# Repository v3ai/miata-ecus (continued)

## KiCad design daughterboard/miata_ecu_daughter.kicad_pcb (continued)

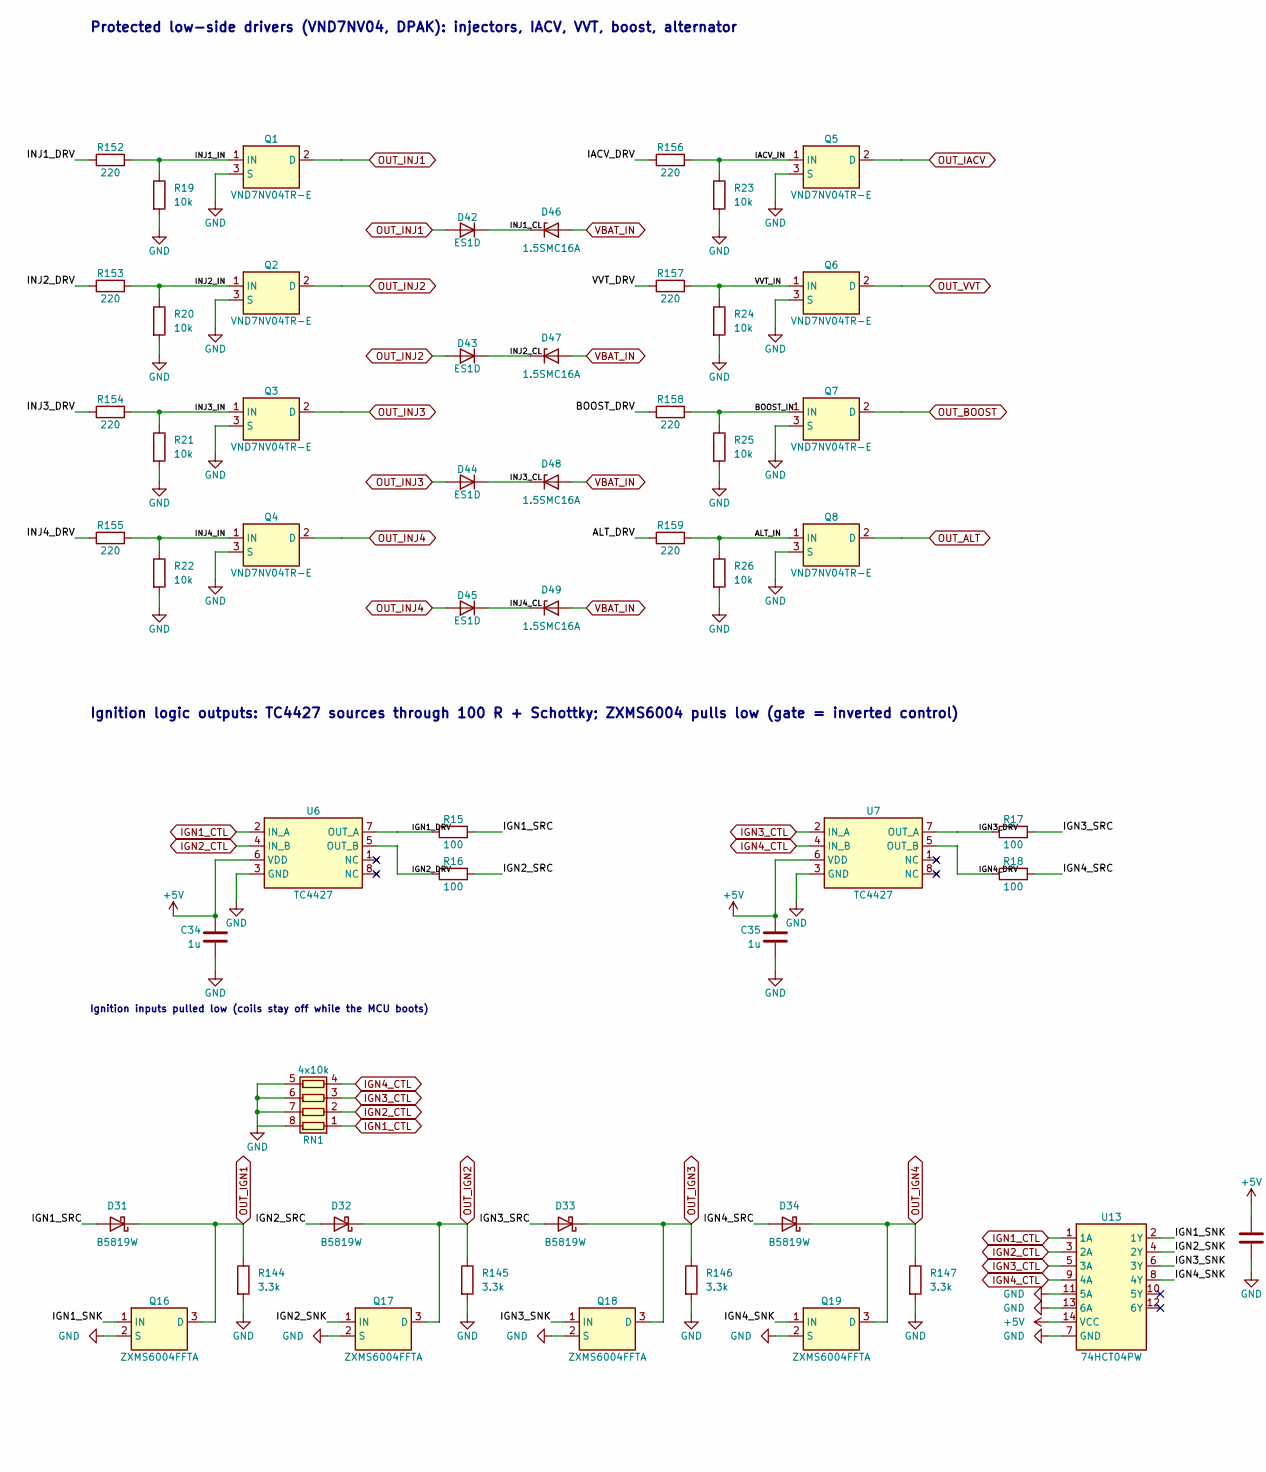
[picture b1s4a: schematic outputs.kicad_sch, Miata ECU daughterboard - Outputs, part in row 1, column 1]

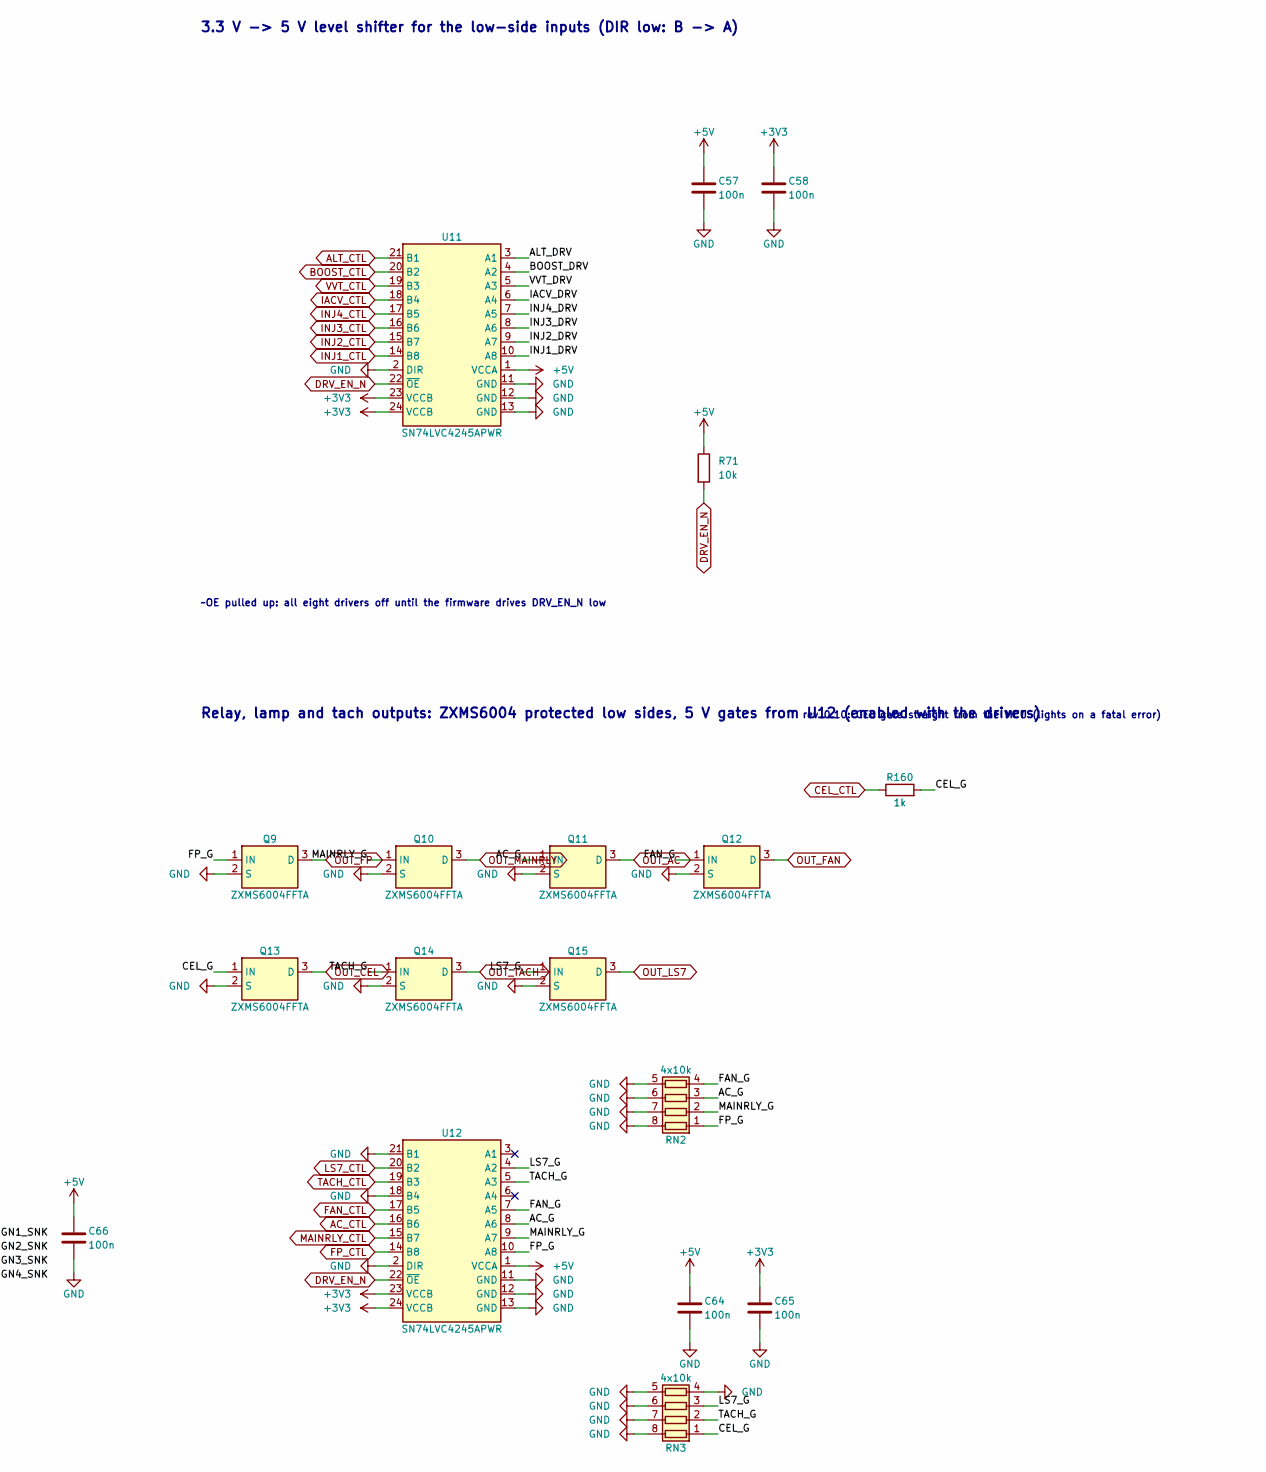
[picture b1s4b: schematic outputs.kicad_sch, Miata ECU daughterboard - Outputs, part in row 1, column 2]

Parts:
C34, C35: 1u; C_0402_1005Metric; LCSC C52923
C57, C58, C64, C65, C66: 100n; C_0402_1005Metric; LCSC C1525
D31, D32, D33, D34: B5819W; D_SOD-123; LCSC C8598
D42, D43, D44, D45: ES1D; D_SMA; LCSC C116492
D46, D47, D48, D49: 1.5SMC16A; D_SMC; LCSC C1973780
Q1, Q2, Q3, Q4, Q5, Q6, Q7, Q8: VND7NV04TR-E; TO-252-2; LCSC C155605
Q9, Q10, Q11, Q12, Q13, Q14, Q15, Q16, Q17, Q18, Q19: ZXMS6004FFTA; SOT-23; LCSC C95063
R15, R16, R17, R18: 100; R_1206_3216Metric; LCSC C17901
R19, R20, R21, R22, R23, R24, R25, R26: 10k; R_0603_1608Metric; LCSC C25804
R71: 10k; R_0402_1005Metric; LCSC C25744
R144, R145, R146, R147: 3.3k; R_1206_3216Metric; LCSC C26032
R152, R153, R154, R155, R156, R157, R158, R159: 220; R_0402_1005Metric; LCSC C25091
R160: 1k; R_0402_1005Metric; LCSC C11702
RN1, RN2, RN3: 4x10k; R_Array_Convex_4x0603; LCSC C29718
U6, U7: TC4427; SOIC-8_3.9x4.9mm_P1.27mm; LCSC C20551
U11, U12: SN74LVC4245APWR; TSSOP-24_4.4x7.8mm_P0.65mm; LCSC C7859
U13: 74HCT04PW; TSSOP-14_4.4x5mm_P0.65mm; LCSC C131317

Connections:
+3V3: C58.1, C65.1, U11.23 (VCCB), U11.24 (VCCB), U12.23 (VCCB), U12.24 (VCCB); also elsewhere on the board
+5V: C34.1, C35.1, C57.1, C64.1, C66.1, R71.1, U6.6 (VDD), U7.6 (VDD), U11.1 (VCCA), U12.1 (VCCA), U13.14 (VCC); also elsewhere on the board
/Outputs/AC_G: Q11.1 (IN), RN2.3 (R3.1), U12.8 (A6)
/Outputs/ALT_DRV: R159.1, U11.3 (A1)
/Outputs/ALT_IN: Q8.1 (IN), R26.1, R159.2
/Outputs/BOOST_DRV: R158.1, U11.4 (A2)
/Outputs/BOOST_IN: Q7.1 (IN), R25.1, R158.2
/Outputs/CEL_G: Q13.1 (IN), R160.2, RN3.1 (R1.1)
/Outputs/FAN_G: Q12.1 (IN), RN2.4 (R4.1), U12.7 (A5)
/Outputs/FP_G: Q9.1 (IN), RN2.1 (R1.1), U12.10 (A8)
/Outputs/IACV_DRV: R156.1, U11.6 (A4)
/Outputs/IACV_IN: Q5.1 (IN), R23.1, R156.2
/Outputs/IGN1_DRV: R15.1, U6.7 (OUT_A)
/Outputs/IGN1_SNK: Q16.1 (IN), U13.2 (1Y)
/Outputs/IGN1_SRC: D31.2 (A), R15.2
/Outputs/IGN2_DRV: R16.1, U6.5 (OUT_B)
/Outputs/IGN2_SNK: Q17.1 (IN), U13.4 (2Y)
/Outputs/IGN2_SRC: D32.2 (A), R16.2
/Outputs/IGN3_DRV: R17.1, U7.7 (OUT_A)
/Outputs/IGN3_SNK: Q18.1 (IN), U13.6 (3Y)
/Outputs/IGN3_SRC: D33.2 (A), R17.2
/Outputs/IGN4_DRV: R18.1, U7.5 (OUT_B)
/Outputs/IGN4_SNK: Q19.1 (IN), U13.8 (4Y)
/Outputs/IGN4_SRC: D34.2 (A), R18.2
/Outputs/INJ1_CL: D42.1 (K), D46.1 (K)
/Outputs/INJ1_DRV: R152.1, U11.10 (A8)
/Outputs/INJ1_IN: Q1.1 (IN), R19.1, R152.2
/Outputs/INJ2_CL: D43.1 (K), D47.1 (K)
/Outputs/INJ2_DRV: R153.1, U11.9 (A7)
/Outputs/INJ2_IN: Q2.1 (IN), R20.1, R153.2
/Outputs/INJ3_CL: D44.1 (K), D48.1 (K)
/Outputs/INJ3_DRV: R154.1, U11.8 (A6)
/Outputs/INJ3_IN: Q3.1 (IN), R21.1, R154.2
/Outputs/INJ4_CL: D45.1 (K), D49.1 (K)
/Outputs/INJ4_DRV: R155.1, U11.7 (A5)
/Outputs/INJ4_IN: Q4.1 (IN), R22.1, R155.2
/Outputs/LS7_G: Q15.1 (IN), RN3.3 (R3.1), U12.4 (A2)
/Outputs/MAINRLY_G: Q10.1 (IN), RN2.2 (R2.1), U12.9 (A7)
/Outputs/TACH_G: Q14.1 (IN), RN3.2 (R2.1), U12.5 (A3)
/Outputs/VVT_DRV: R157.1, U11.5 (A3)
/Outputs/VVT_IN: Q6.1 (IN), R24.1, R157.2
AC_CTL: U12.16 (B6); also elsewhere on the board
ALT_CTL: U11.21 (B1); also elsewhere on the board
BOOST_CTL: U11.20 (B2); also elsewhere on the board
CEL_CTL: R160.1; also elsewhere on the board
DRV_EN_N: R71.2, U11.22 (~OE), U12.22 (~OE); also elsewhere on the board
FAN_CTL: U12.17 (B5); also elsewhere on the board
FP_CTL: U12.14 (B8); also elsewhere on the board
GND: C34.2, C35.2, C57.2, C58.2, C64.2, C65.2, C66.2, Q1.3 (S), Q2.3 (S), Q3.3 (S), Q4.3 (S), Q5.3 (S), Q6.3 (S), Q7.3 (S), Q8.3 (S), Q9.2 (S), Q10.2 (S), Q11.2 (S), Q12.2 (S), Q13.2 (S), Q14.2 (S), Q15.2 (S), Q16.2 (S), Q17.2 (S), Q18.2 (S), Q19.2 (S), R19.2, R20.2, R21.2, R22.2, R23.2, R24.2, R25.2, R26.2, R144.2, R145.2, R146.2, R147.2, RN1.5 (R4.2), RN1.6 (R3.2), RN1.7 (R2.2), RN1.8 (R1.2), RN2.5 (R4.2), RN2.6 (R3.2), RN2.7 (R2.2), RN2.8 (R1.2), RN3.4 (R4.1), RN3.5 (R4.2), RN3.6 (R3.2), RN3.7 (R2.2), RN3.8 (R1.2), U6.3 (GND), U7.3 (GND), U11.2 (DIR), U11.11 (GND), U11.12 (GND), U11.13 (GND), U12.2 (DIR), U12.11 (GND), U12.12 (GND), U12.13 (GND), U12.18 (B4), U12.21 (B1), U13.7 (GND), U13.11 (5A), U13.13 (6A); also elsewhere on the board
IACV_CTL: U11.18 (B4); also elsewhere on the board
IGN1_CTL: RN1.1 (R1.1), U6.2 (IN_A), U13.1 (1A); also elsewhere on the board
IGN2_CTL: RN1.2 (R2.1), U6.4 (IN_B), U13.3 (2A); also elsewhere on the board
IGN3_CTL: RN1.3 (R3.1), U7.2 (IN_A), U13.5 (3A); also elsewhere on the board
IGN4_CTL: RN1.4 (R4.1), U7.4 (IN_B), U13.9 (4A); also elsewhere on the board
INJ1_CTL: U11.14 (B8); also elsewhere on the board
INJ2_CTL: U11.15 (B7); also elsewhere on the board
INJ3_CTL: U11.16 (B6); also elsewhere on the board
INJ4_CTL: U11.17 (B5); also elsewhere on the board
LS7_CTL: U12.20 (B2); also elsewhere on the board
MAINRLY_CTL: U12.15 (B7); also elsewhere on the board
OUT_AC: Q11.3 (D); also elsewhere on the board
OUT_ALT: Q8.2 (D); also elsewhere on the board
OUT_BOOST: Q7.2 (D); also elsewhere on the board
OUT_CEL: Q13.3 (D); also elsewhere on the board
OUT_FAN: Q12.3 (D); also elsewhere on the board
OUT_FP: Q9.3 (D); also elsewhere on the board
OUT_IACV: Q5.2 (D); also elsewhere on the board
OUT_IGN1: D31.1 (K), Q16.3 (D), R144.1; also elsewhere on the board
OUT_IGN2: D32.1 (K), Q17.3 (D), R145.1; also elsewhere on the board
OUT_IGN3: D33.1 (K), Q18.3 (D), R146.1; also elsewhere on the board
OUT_IGN4: D34.1 (K), Q19.3 (D), R147.1; also elsewhere on the board
OUT_INJ1: D42.2 (A), Q1.2 (D); also elsewhere on the board
OUT_INJ2: D43.2 (A), Q2.2 (D); also elsewhere on the board
OUT_INJ3: D44.2 (A), Q3.2 (D); also elsewhere on the board
OUT_INJ4: D45.2 (A), Q4.2 (D); also elsewhere on the board
OUT_LS7: Q15.3 (D); also elsewhere on the board
OUT_MAINRLY: Q10.3 (D); also elsewhere on the board
OUT_TACH: Q14.3 (D); also elsewhere on the board
OUT_VVT: Q6.2 (D); also elsewhere on the board
TACH_CTL: U12.19 (B3); also elsewhere on the board
VBAT_IN: D46.2 (A), D47.2 (A), D48.2 (A), D49.2 (A); also elsewhere on the board
VVT_CTL: U11.19 (B3); also elsewhere on the board

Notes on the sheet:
Protected low-side drivers (VND7NV04, DPAK): injectors, IACV, VVT, boost, alternator
Ignition logic outputs: TC4427 sources through 100 R + Schottky; ZXMS6004 pulls low (gate = inverted control)
Ignition inputs pulled low (coils stay off while the MCU boots)
Relay, lamp and tach outputs: ZXMS6004 protected low sides, 5 V gates from U12 (enabled with the drivers)
rev 0.10: CEL gate straight from the MCU (lights on a fatal error)
3.3 V -> 5 V level shifter for the low-side inputs (DIR low: B -> A)
~OE pulled up: all eight drivers off until the firmware drives DRV_EN_N low

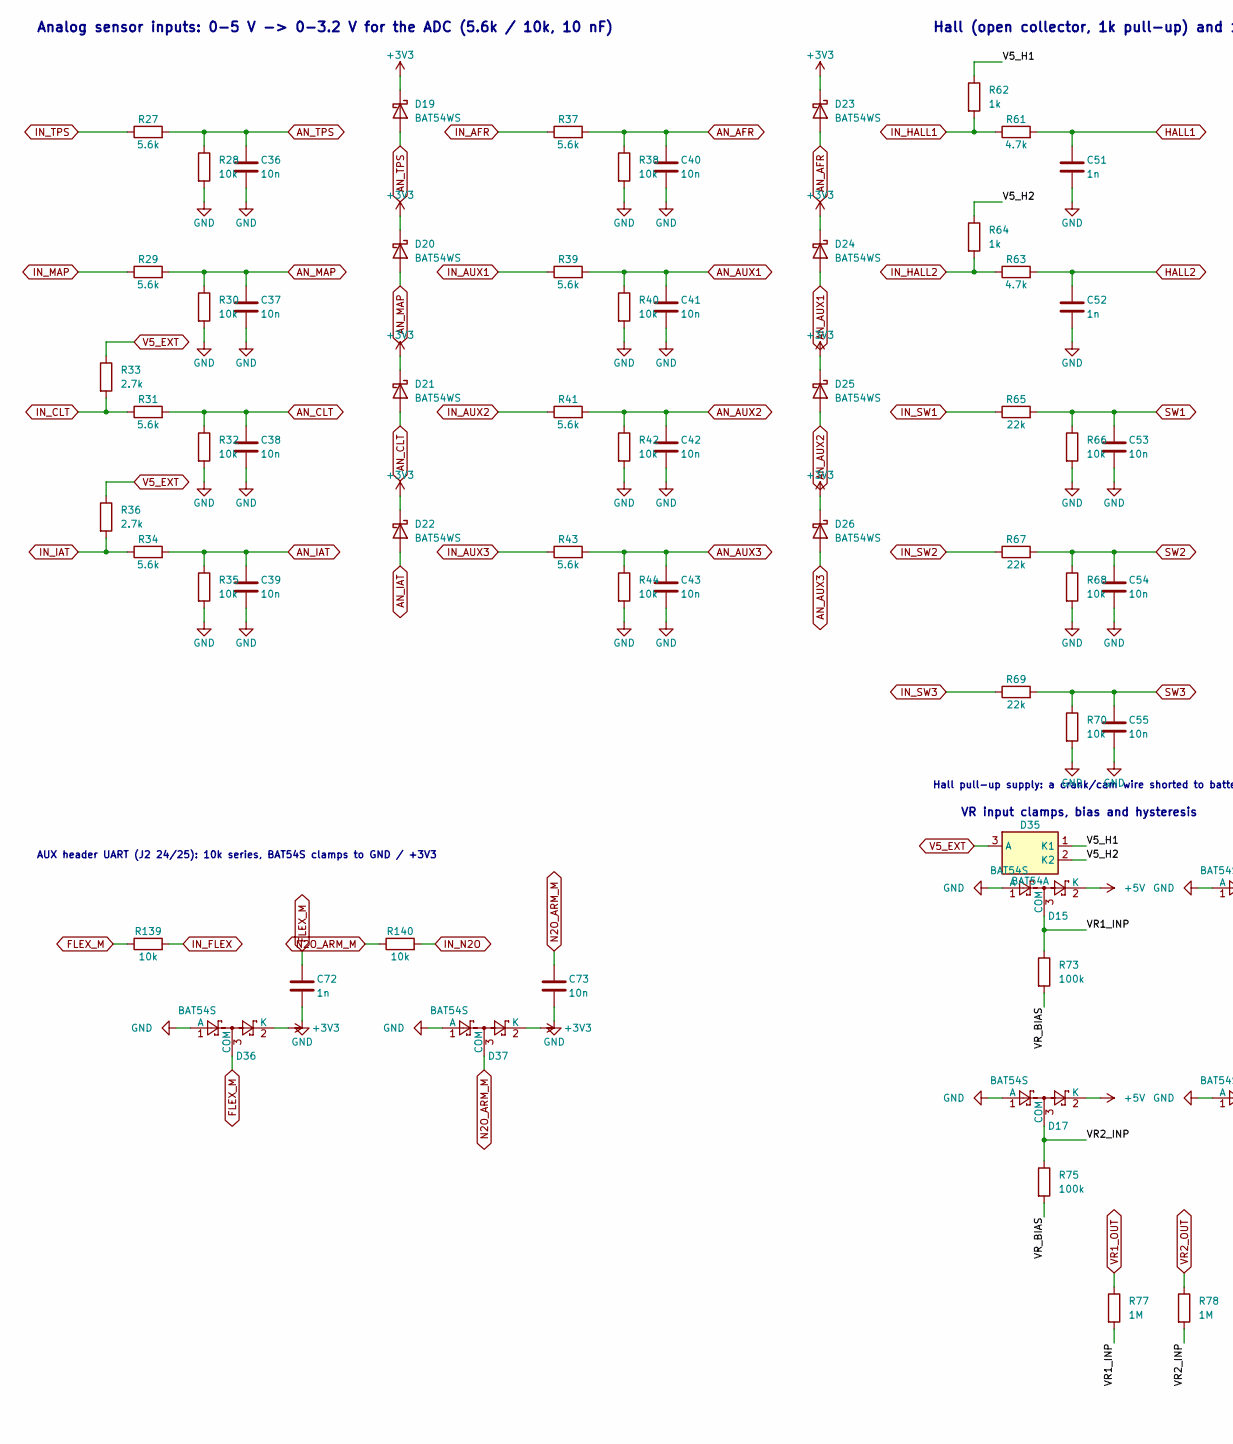
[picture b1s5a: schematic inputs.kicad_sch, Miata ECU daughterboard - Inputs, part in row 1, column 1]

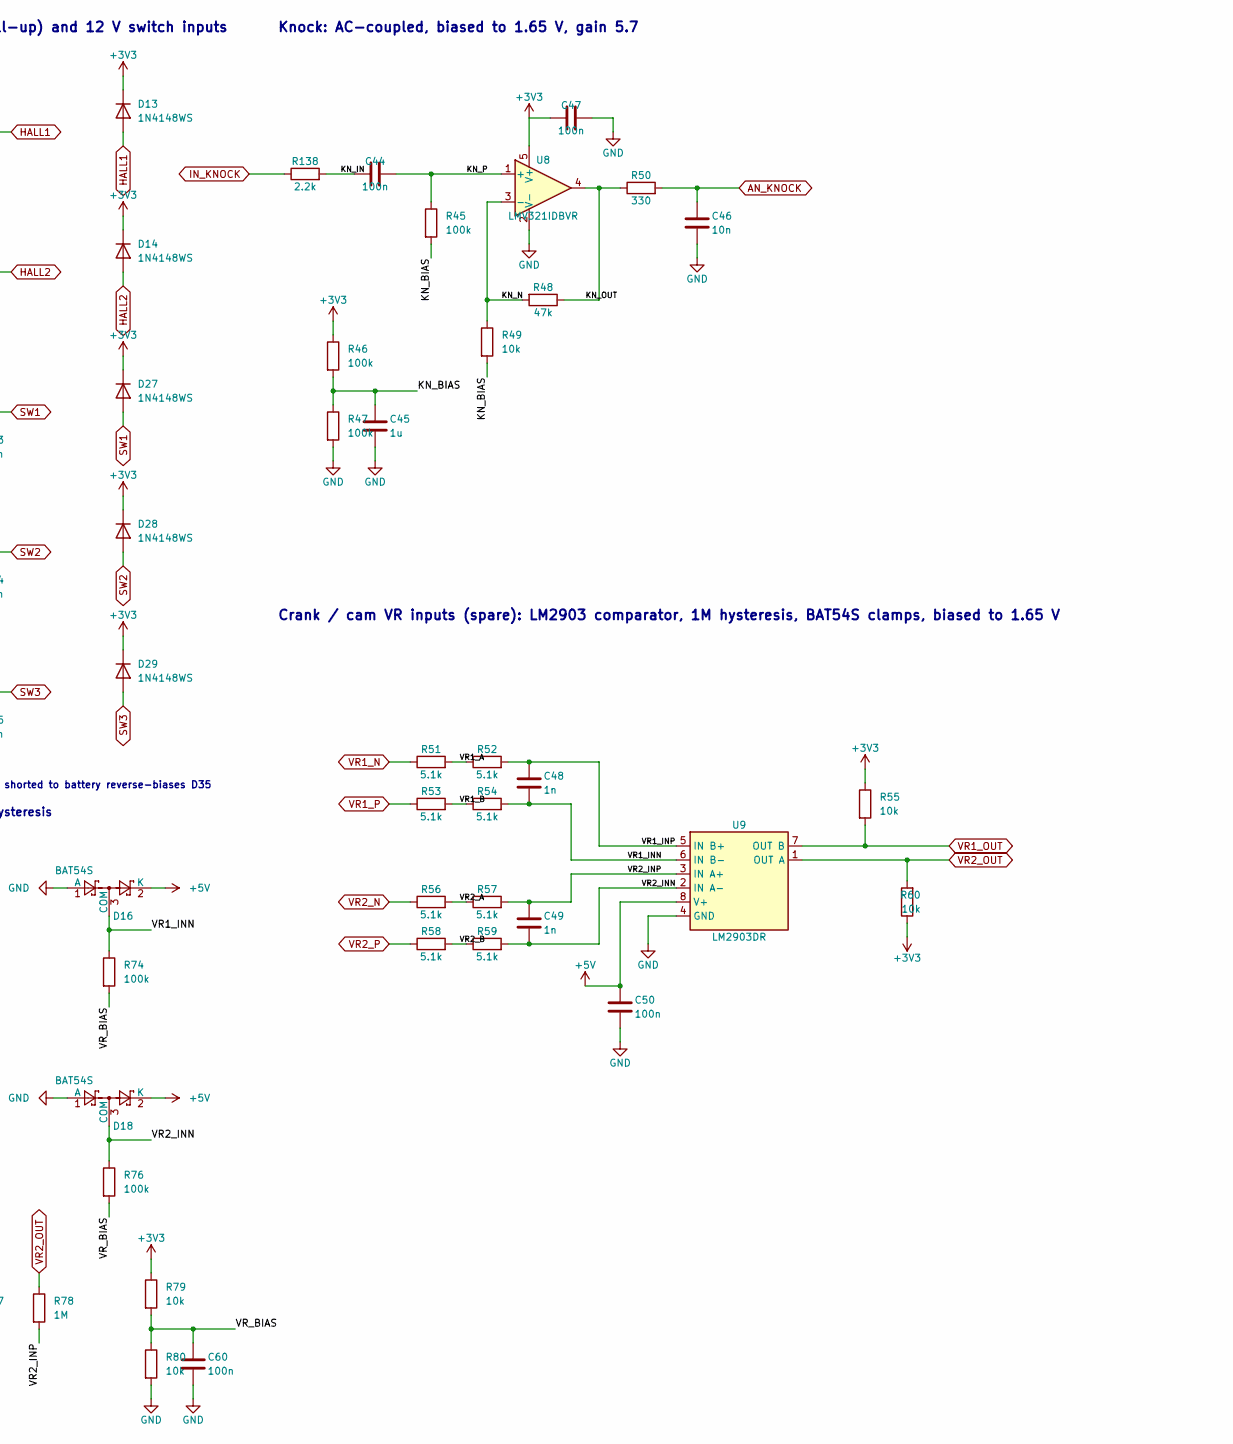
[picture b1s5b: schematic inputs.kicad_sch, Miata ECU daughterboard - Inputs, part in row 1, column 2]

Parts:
C36, C37, C38, C39, C40, C41, C42, C43, C53, C54, C55, C73: 10n; C_0402_1005Metric; LCSC C15195
C44, C47, C50: 100n; C_0603_1608Metric; LCSC C14663
C45: 1u; C_0603_1608Metric; LCSC C15849
C46: 10n; C_0603_1608Metric; LCSC C57112
C48, C49: 1n; C_0805_2012Metric; LCSC C46653
C51, C52, C72: 1n; C_0402_1005Metric; LCSC C1523
C60: 100n; C_0402_1005Metric; LCSC C1525
D13, D14, D27, D28, D29: 1N4148WS; D_SOD-323; LCSC C2128
D15, D16, D17, D18, D36, D37: BAT54S; SOT-23; LCSC C19726
D19, D20, D21, D22, D23, D24, D25, D26: BAT54WS; D_SOD-323; LCSC C124205
D35: BAT54A; SOT-23; LCSC C916423
R27, R29, R31, R34, R37, R39, R41, R43: 5.6k; R_0603_1608Metric; LCSC C23189
R28, R30, R32, R35, R38, R40, R42, R44, R66, R68, R70, R79, R80: 10k; R_0402_1005Metric; LCSC C25744
R33, R36: 2.7k; R_0603_1608Metric; LCSC C13167
R45, R46, R47: 100k; R_0603_1608Metric; LCSC C25803
R48: 47k; R_0603_1608Metric; LCSC C25819
R49, R55, R60, R139, R140: 10k; R_0603_1608Metric; LCSC C25804
R50: 330; R_0603_1608Metric; LCSC C23138
R51, R52, R53, R54, R56, R57, R58, R59: 5.1k; R_0805_2012Metric; LCSC C27834
R61, R63: 4.7k; R_0603_1608Metric; LCSC C23162
R62, R64: 1k; R_0603_1608Metric; LCSC C21190
R65, R67, R69: 22k; R_0402_1005Metric; LCSC C25768
R73, R74, R75, R76: 100k; R_0402_1005Metric; LCSC C25741
R77, R78: 1M; R_0402_1005Metric; LCSC C26083
R138: 2.2k; R_0402_1005Metric; LCSC C25879
U8: LMV321IDBVR; SOT-23-5; LCSC C7972
U9: LM2903DR; SOIC-8_3.9x4.9mm_P1.27mm; LCSC C7549

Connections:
+3V3: C47.1, D13.1 (K), D14.1 (K), D19.1 (K), D20.1 (K), D21.1 (K), D22.1 (K), D23.1 (K), D24.1 (K), D25.1 (K), D26.1 (K), D27.1 (K), D28.1 (K), D29.1 (K), D36.2 (K), D37.2 (K), R46.1, R55.1, R60.1, R79.1, U8.5 (V+); also elsewhere on the board
+5V: C50.1, D15.2 (K), D16.2 (K), D17.2 (K), D18.2 (K), U9.8 (V+); also elsewhere on the board
/Inputs/KN_BIAS: C45.1, R45.2, R46.2, R47.1, R49.2
/Inputs/KN_IN: C44.1, R138.2
/Inputs/KN_N: R48.2, R49.1, U8.3 (-)
/Inputs/KN_OUT: R48.1, R50.1, U8.4
/Inputs/KN_P: C44.2, R45.1, U8.1 (+)
/Inputs/V5_H1: D35.1 (K1), R62.1
/Inputs/V5_H2: D35.2 (K2), R64.1
/Inputs/VR1_A: R51.2, R52.1
/Inputs/VR1_B: R53.2, R54.1
/Inputs/VR1_INN: C48.2, D16.3 (COM), R54.2, R74.1, U9.6 (IN B-)
/Inputs/VR1_INP: C48.1, D15.3 (COM), R52.2, R73.1, R77.2, U9.5 (IN B+)
/Inputs/VR2_A: R56.2, R57.1
/Inputs/VR2_B: R58.2, R59.1
/Inputs/VR2_INN: C49.2, D18.3 (COM), R59.2, R76.1, U9.2 (IN A-)
/Inputs/VR2_INP: C49.1, D17.3 (COM), R57.2, R75.1, R78.2, U9.3 (IN A+)
/Inputs/VR_BIAS: C60.1, R73.2, R74.2, R75.2, R76.2, R79.2, R80.1
AN_AFR: C40.1, D23.2 (A), R37.2, R38.1; also elsewhere on the board
AN_AUX1: C41.1, D24.2 (A), R39.2, R40.1; also elsewhere on the board
AN_AUX2: C42.1, D25.2 (A), R41.2, R42.1; also elsewhere on the board
AN_AUX3: C43.1, D26.2 (A), R43.2, R44.1; also elsewhere on the board
AN_CLT: C38.1, D21.2 (A), R31.2, R32.1; also elsewhere on the board
AN_IAT: C39.1, D22.2 (A), R34.2, R35.1; also elsewhere on the board
AN_KNOCK: C46.1, R50.2; also elsewhere on the board
AN_MAP: C37.1, D20.2 (A), R29.2, R30.1; also elsewhere on the board
AN_TPS: C36.1, D19.2 (A), R27.2, R28.1; also elsewhere on the board
FLEX_M: C72.1, D36.3 (COM), R139.1; also elsewhere on the board
GND: C36.2, C37.2, C38.2, C39.2, C40.2, C41.2, C42.2, C43.2, C45.2, C46.2, C47.2, C50.2, C51.2, C52.2, C53.2, C54.2, C55.2, C60.2, C72.2, C73.2, D15.1 (A), D16.1 (A), D17.1 (A), D18.1 (A), D36.1 (A), D37.1 (A), R28.2, R30.2, R32.2, R35.2, R38.2, R40.2, R42.2, R44.2, R47.2, R66.2, R68.2, R70.2, R80.2, U8.2 (V-), U9.4 (GND); also elsewhere on the board
HALL1: C51.1, D13.2 (A), R61.2; also elsewhere on the board
HALL2: C52.1, D14.2 (A), R63.2; also elsewhere on the board
IN_AFR: R37.1; also elsewhere on the board
IN_AUX1: R39.1; also elsewhere on the board
IN_AUX2: R41.1; also elsewhere on the board
IN_AUX3: R43.1; also elsewhere on the board
IN_CLT: R31.1, R33.2; also elsewhere on the board
IN_FLEX: R139.2; also elsewhere on the board
IN_HALL1: R61.1, R62.2; also elsewhere on the board
IN_HALL2: R63.1, R64.2; also elsewhere on the board
IN_IAT: R34.1, R36.2; also elsewhere on the board
IN_KNOCK: R138.1; also elsewhere on the board
IN_MAP: R29.1; also elsewhere on the board
IN_N2O: R140.2; also elsewhere on the board
IN_SW1: R65.1; also elsewhere on the board
IN_SW2: R67.1; also elsewhere on the board
IN_SW3: R69.1; also elsewhere on the board
IN_TPS: R27.1; also elsewhere on the board
N2O_ARM_M: C73.1, D37.3 (COM), R140.1; also elsewhere on the board
SW1: C53.1, D27.2 (A), R65.2, R66.1; also elsewhere on the board
SW2: C54.1, D28.2 (A), R67.2, R68.1; also elsewhere on the board
SW3: C55.1, D29.2 (A), R69.2, R70.1; also elsewhere on the board
V5_EXT: D35.3 (A), R33.1, R36.1; also elsewhere on the board
VR1_N: R51.1; also elsewhere on the board
VR1_OUT: R55.2, R77.1, U9.7 (OUT B); also elsewhere on the board
VR1_P: R53.1; also elsewhere on the board
VR2_N: R56.1; also elsewhere on the board
VR2_OUT: R60.2, R78.1, U9.1 (OUT A); also elsewhere on the board
VR2_P: R58.1; also elsewhere on the board

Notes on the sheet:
Analog sensor inputs: 0-5 V -> 0-3.2 V for the ADC (5.6k / 10k, 10 nF)
Hall (open collector, 1k pull-up) and 12 V switch inputs
Hall pull-up supply: a crank/cam wire shorted to battery reverse-biases D35
AUX header UART (J2 24/25): 10k series, BAT54S clamps to GND / +3V3
Knock: AC-coupled, biased to 1.65 V, gain 5.7
Crank / cam VR inputs (spare): LM2903 comparator, 1M hysteresis, BAT54S clamps, biased to 1.65 V
VR input clamps, bias and hysteresis

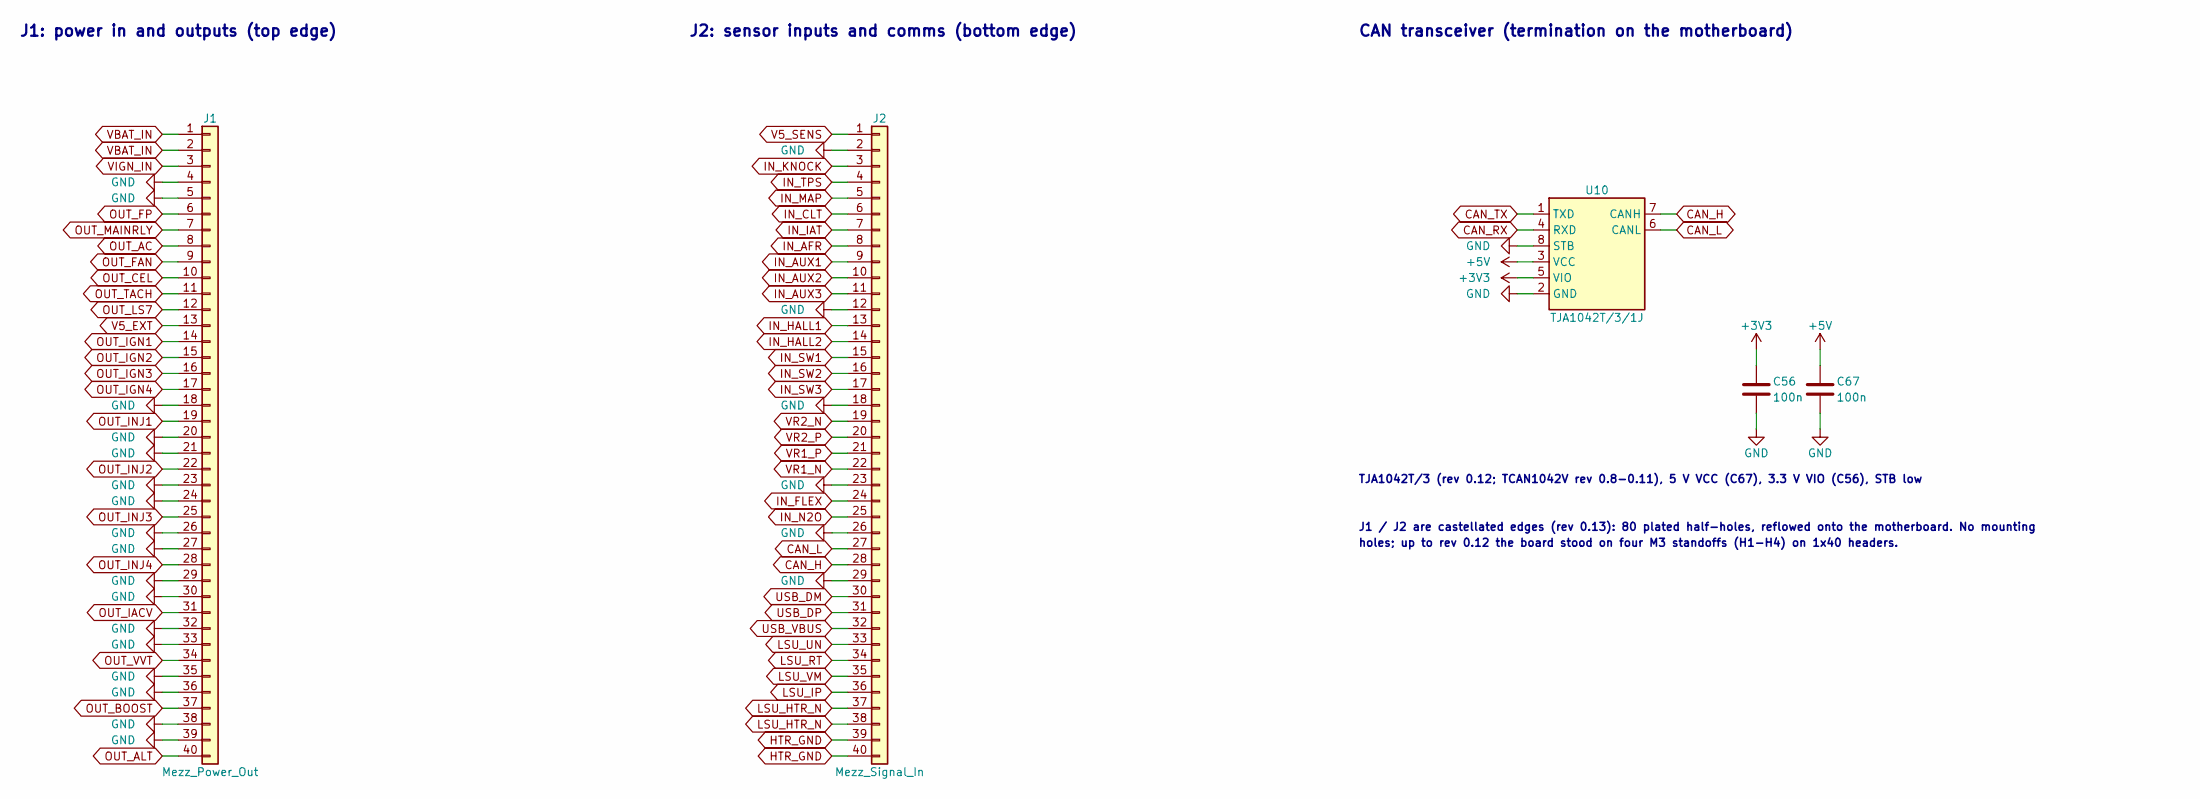
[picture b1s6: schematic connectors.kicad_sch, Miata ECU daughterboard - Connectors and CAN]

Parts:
C56: 100n; C_0603_1608Metric; LCSC C14663
C67: 100n; C_0402_1005Metric; LCSC C1525
J1: Mezz_Power_Out; Castellated_1x40_P2.54mm
J2: Mezz_Signal_In; Castellated_1x40_P2.54mm
U10: TJA1042T/3/1J; SOIC-8_3.9x4.9mm_P1.27mm; LCSC C132227

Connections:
+3V3: C56.1, U10.5 (VIO); also elsewhere on the board
+5V: C67.1, U10.3 (VCC); also elsewhere on the board
CAN_H: J2.28, U10.7 (CANH); also elsewhere on the board
CAN_L: J2.27, U10.6 (CANL); also elsewhere on the board
CAN_RX: U10.4 (RXD); also elsewhere on the board
CAN_TX: U10.1 (TXD); also elsewhere on the board
GND: C56.2, C67.2, J1.4, J1.5, J1.18, J1.20, J1.21, J1.23, J1.24, J1.26, J1.27, J1.29, J1.30, J1.32, J1.33, J1.35, J1.36, J1.38, J1.39, J2.2, J2.12, J2.18, J2.23, J2.26, J2.29, U10.2 (GND), U10.8 (STB); also elsewhere on the board
HTR_GND: J2.39, J2.40; also elsewhere on the board
IN_AFR: J2.8; also elsewhere on the board
IN_AUX1: J2.9; also elsewhere on the board
IN_AUX2: J2.10; also elsewhere on the board
IN_AUX3: J2.11; also elsewhere on the board
IN_CLT: J2.6; also elsewhere on the board
IN_FLEX: J2.24; also elsewhere on the board
IN_HALL1: J2.13; also elsewhere on the board
IN_HALL2: J2.14; also elsewhere on the board
IN_IAT: J2.7; also elsewhere on the board
IN_KNOCK: J2.3; also elsewhere on the board
IN_MAP: J2.5; also elsewhere on the board
IN_N2O: J2.25; also elsewhere on the board
IN_SW1: J2.15; also elsewhere on the board
IN_SW2: J2.16; also elsewhere on the board
IN_SW3: J2.17; also elsewhere on the board
IN_TPS: J2.4; also elsewhere on the board
LSU_HTR_N: J2.37, J2.38; also elsewhere on the board
LSU_IP: J2.36; also elsewhere on the board
LSU_RT: J2.34; also elsewhere on the board
LSU_UN: J2.33; also elsewhere on the board
LSU_VM: J2.35; also elsewhere on the board
OUT_AC: J1.8; also elsewhere on the board
OUT_ALT: J1.40; also elsewhere on the board
OUT_BOOST: J1.37; also elsewhere on the board
OUT_CEL: J1.10; also elsewhere on the board
OUT_FAN: J1.9; also elsewhere on the board
OUT_FP: J1.6; also elsewhere on the board
OUT_IACV: J1.31; also elsewhere on the board
OUT_IGN1: J1.14; also elsewhere on the board
OUT_IGN2: J1.15; also elsewhere on the board
OUT_IGN3: J1.16; also elsewhere on the board
OUT_IGN4: J1.17; also elsewhere on the board
OUT_INJ1: J1.19; also elsewhere on the board
OUT_INJ2: J1.22; also elsewhere on the board
OUT_INJ3: J1.25; also elsewhere on the board
OUT_INJ4: J1.28; also elsewhere on the board
OUT_LS7: J1.12; also elsewhere on the board
OUT_MAINRLY: J1.7; also elsewhere on the board
OUT_TACH: J1.11; also elsewhere on the board
OUT_VVT: J1.34; also elsewhere on the board
USB_DM: J2.30; also elsewhere on the board
USB_DP: J2.31; also elsewhere on the board
USB_VBUS: J2.32; also elsewhere on the board
V5_EXT: J1.13; also elsewhere on the board
V5_SENS: J2.1; also elsewhere on the board
VBAT_IN: J1.1, J1.2; also elsewhere on the board
VIGN_IN: J1.3; also elsewhere on the board
VR1_N: J2.22; also elsewhere on the board
VR1_P: J2.21; also elsewhere on the board
VR2_N: J2.19; also elsewhere on the board
VR2_P: J2.20; also elsewhere on the board

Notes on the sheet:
J1: power in and outputs (top edge)
J2: sensor inputs and comms (bottom edge)
CAN transceiver (termination on the motherboard)
TJA1042T/3 (rev 0.12; TCAN1042V rev 0.8-0.11), 5 V VCC (C67), 3.3 V VIO (C56), STB low
J1 / J2 are castellated edges (rev 0.13): 80 plated half-holes, reflowed onto the motherboard. No mounting
holes; up to rev 0.12 the board stood on four M3 standoffs (H1-H4) on 1x40 headers.
